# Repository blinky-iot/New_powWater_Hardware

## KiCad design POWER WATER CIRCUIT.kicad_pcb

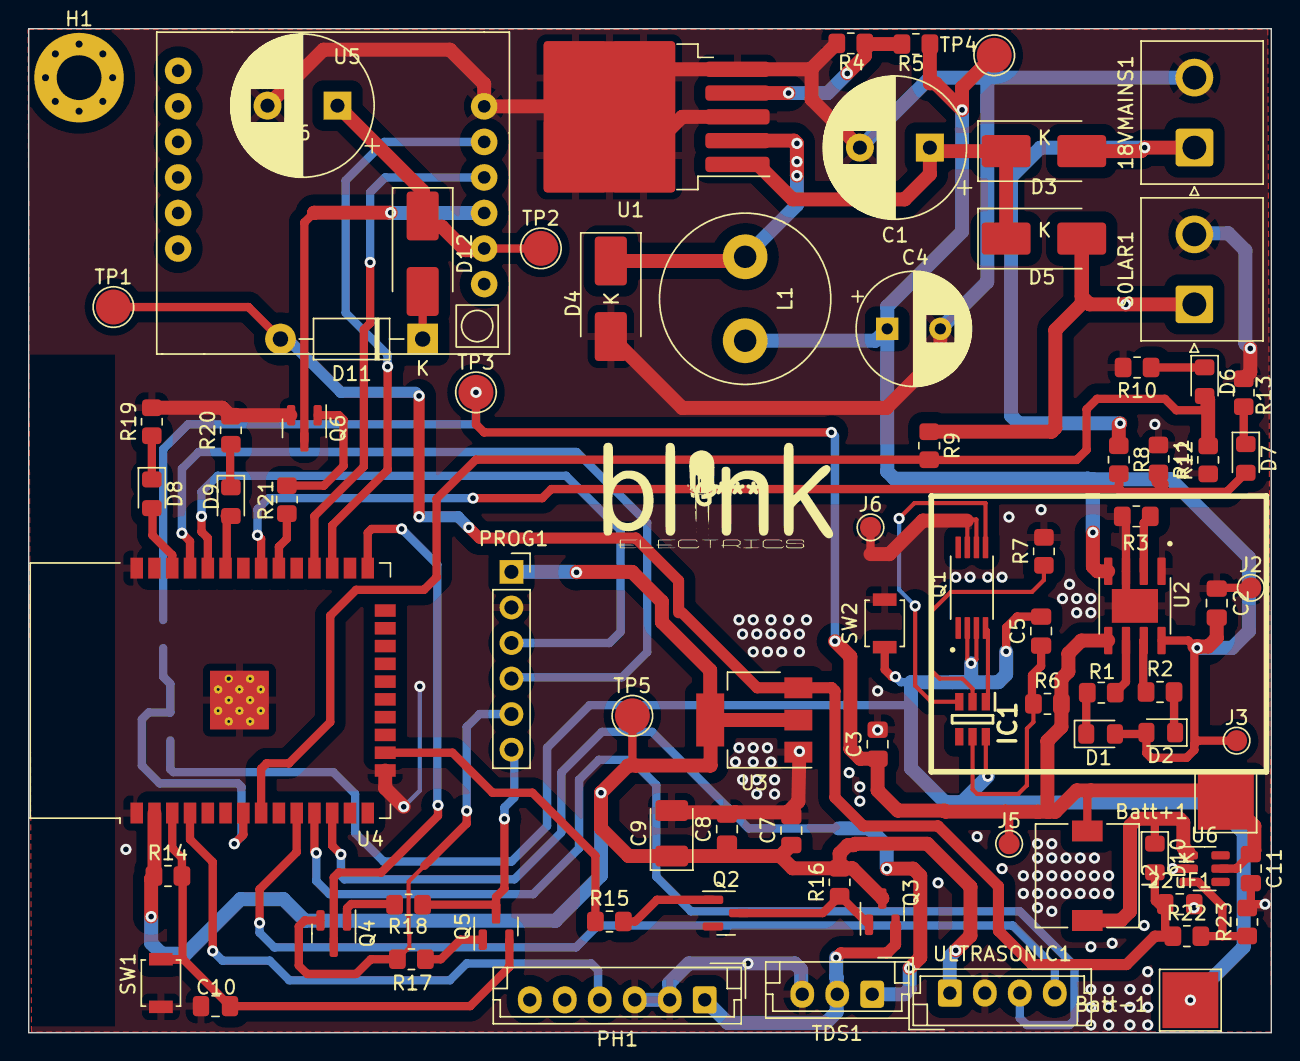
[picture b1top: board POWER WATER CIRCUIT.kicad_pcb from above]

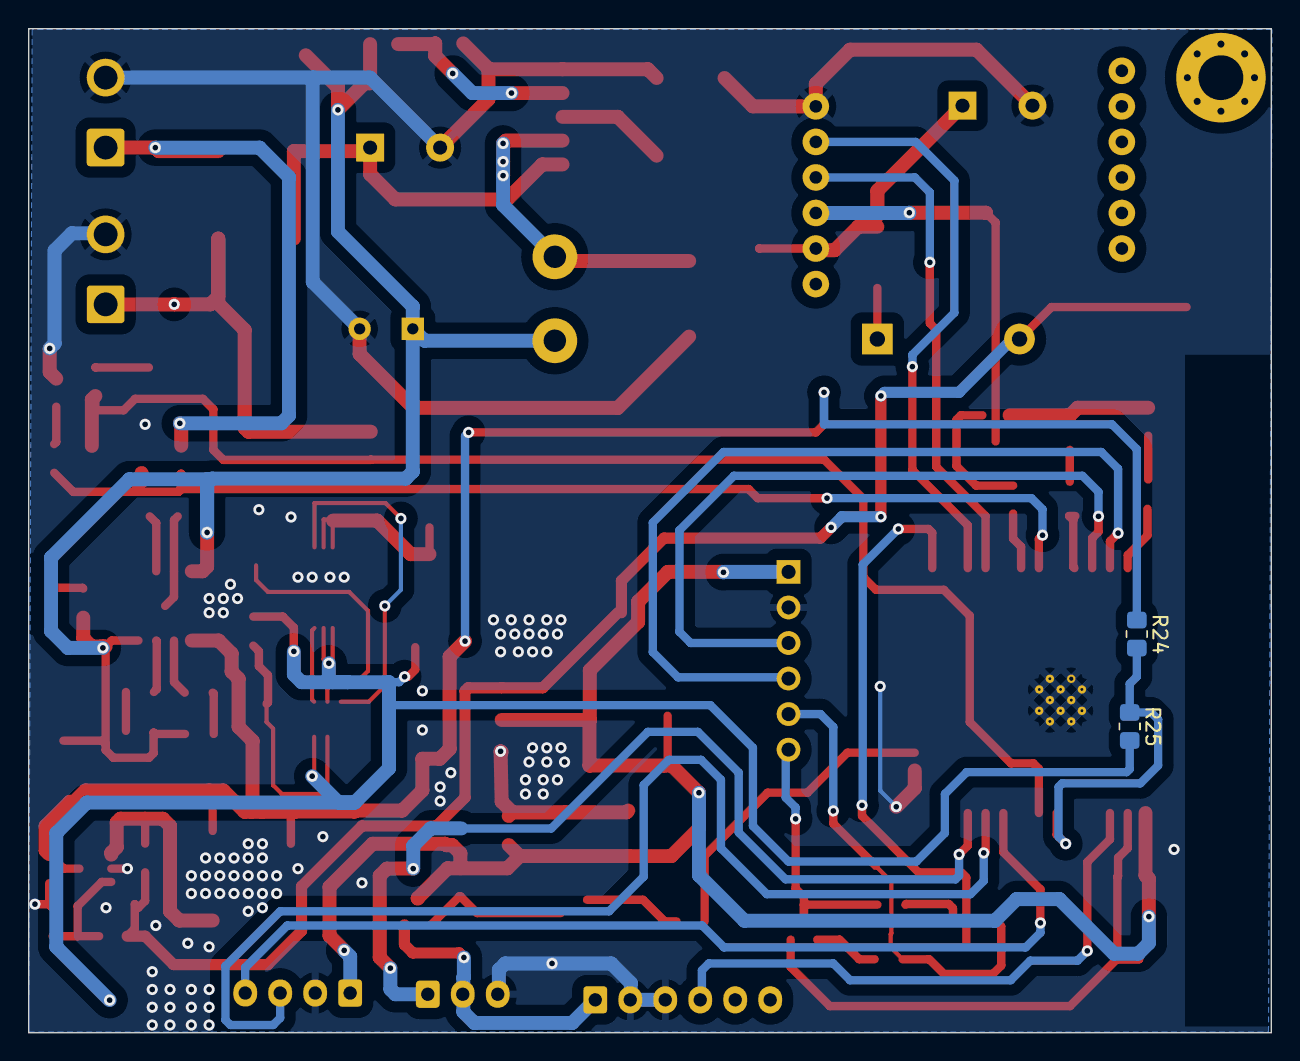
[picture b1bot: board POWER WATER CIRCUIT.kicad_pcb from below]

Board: 2 copper layers, 88.8 x 71.8 mm, 84 parts (2 on the bottom side), 54 nets.

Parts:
18VMAINS1: Screw_Terminal_01x02; JST_NV_B02P-NV_1x02_P5.00mm_Vertical
22uF1: C; C_0805_2012Metric_Pad1.18x1.45mm_HandSolder
Batt+1: BatteryPositive; TestPoint_Pad_4.0x4.0mm
Batt-1: BatteryNegative; TestPoint_Pad_4.0x4.0mm
C1, C6: 470uF; CP_Radial_D10.0mm_P5.00mm
C2, C3, C5, C7, C8, C10: 0.1uF; C_0805_2012Metric_Pad1.18x1.45mm_HandSolder
C4: 220uF; CP_Radial_D8.0mm_P3.80mm
C9: 220uF; CP_EIA-3528-15_AVX-H_Pad1.50x2.35mm_HandSolder
C11: 22UF; C_0805_2012Metric_Pad1.18x1.45mm_HandSolder
D1, D6, D8: GREEN_LED; LED_0805_2012Metric_Pad1.15x1.40mm_HandSolder
D2, D7, D9: RED_LED; LED_0805_2012Metric_Pad1.15x1.40mm_HandSolder
D3, D5, D12: 1N5820; D_SMB_Handsoldering
D4: 1N5819; D_SMB_Handsoldering
D10: 1N5820; D_0805_2012Metric_Pad1.15x1.40mm_HandSolder
D11: 1N4007; D_DO-41_SOD81_P10.16mm_Horizontal
H1: MountingHole_Pad; MountingHole_3.2mm_M3_Pad_Via
IC1: DW01; SOT95P280X135-6N
J2: IN-; TestPoint_Pad_D1.5mm
J3: IN+; TestPoint_Pad_D1.5mm
J5: OUT +; TestPoint_Pad_D1.5mm
J6: OUT -; TestPoint_Pad_D1.5mm
L1: 33uH; L_Radial_D12.0mm_P6.00mm_Murata_1900R
L2: 220uH; L_7.3x7.3_H3.5
PH1: Conn_01x06_Socket; JST_EH_B6B-EH-A_1x06_P2.50mm_Vertical
PROG1: Conn_01x06_Socket; PinSocket_1x06_P2.54mm_Vertical
Q1: FS8205A; SOP65P640X120-8N
Q2, Q4, Q5, Q6: BC817; SOT-23
Q3: IRLML5203; SOT-23
R1, R2, R4, R7: 1K; R_0805_2012Metric_Pad1.20x1.40mm_HandSolder
R3: 1.2K; R_0805_2012Metric_Pad1.20x1.40mm_HandSolder
R5: 3.9k; R_0805_2012Metric_Pad1.20x1.40mm_HandSolder
R6: 100; R_0805_2012Metric_Pad1.20x1.40mm_HandSolder
R8, R9: 10 K; R_0805_2012Metric_Pad1.20x1.40mm_HandSolder
R10, R13, R19, R20: 1k; R_0805_2012Metric_Pad1.20x1.40mm_HandSolder
R11, R12: 2.2 K; R_0805_2012Metric_Pad1.20x1.40mm_HandSolder
R14: 100K; R_0805_2012Metric_Pad1.20x1.40mm_HandSolder
R15: 10k; R_0805_2012Metric_Pad1.20x1.40mm_HandSolder
R16: 100k; R_0805_2012Metric_Pad1.20x1.40mm_HandSolder
R17, R18, R21: 10K; R_0805_2012Metric_Pad1.20x1.40mm_HandSolder
R22: 2.2k; R_0805_2012Metric_Pad1.20x1.40mm_HandSolder
R23: 300; R_0805_2012Metric_Pad1.20x1.40mm_HandSolder
R24: 120k; R_0805_2012Metric_Pad1.20x1.40mm_HandSolder
R25: 440k; R_0805_2012Metric_Pad1.20x1.40mm_HandSolder
S0LAR1: Screw_Terminal_01x02; JST_NV_B02P-NV_1x02_P5.00mm_Vertical
SW1, SW2: SW_MEC_5G; SW_SPST_B3U-1000P
TDS1: Conn_01x03_Socket; JST_EH_B3B-EH-A_1x03_P2.50mm_Vertical
TP1, TP2, TP3, TP4, TP5: TestPoint; TestPoint_Pad_D2.5mm
U1: LM2596S-ADJ; TO-263-5_TabPin3
U2: TP4056; SOP127P600X175-9N
U3: LM1117MP-3.3; SOT-223-3_TabPin2
U4: ESP32-WROOM-32
U5: SIM800L-CORE
U6: MT3608; SOT-23-6
ULTRASONIC1: Conn_01x04_Pin; JST_EH_B4B-EH-A_1x04_P2.50mm_Vertical

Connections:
4.0V: C6.1, D12.1 (K), TP2.1, U5.2 (VCC)
4.2: Batt+1.1, C3.1, C11.1, J5.1, L2.1, R6.2, R24.1, TP3.1, U2.5 (BAT), U6.5 (IN)
5V: 22uF1.1, D10.2 (A), D11.2 (A), R22.1, TP1.1, U3.3 (VI)
6V: C2.1, C4.1, D1.2 (A), D2.2 (A), J3.1, L1.2, R5.2, TP4.1, U2.4 (VCC), U2.8 (CE)
+3.3V: C7.1, C8.1, C9.1, PROG1.1, Q3.2 (S), R14.1, R16.2, TP5.1, U3.2 (VO), U4.2 (VDD), ULTRASONIC1.1
+ 18 V: C1.1, D3.1 (K), D5.1 (K), U1.1 (VIN)
BATERY VOLTAGE: R24.2, R25.1, U4.7 (IO35)
BT -VE: Batt-1.1, C5.2, IC1.6 (VSS), Q1.2 (S1_1), Q1.3 (S1_2), R25.2, SW2.1 (A)
CHRG: R2.1, U2.7 (~CHRG)
DC_Mains: 18VMAINS1.1, D3.2 (A), R8.1
DC_Solar: D5.2 (A), R9.1, S0LAR1.1
DTR: PROG1.5, Q4.2 (E), R17.1
GND: 18VMAINS1.2, 22uF1.2, C1.2, C2.2, C3.2, C4.2, C6.2, C7.2, C8.2, C9.2, C10.2, C11.2, D4.2 (A), J2.1, J6.1, PH1.2, PH1.3, PROG1.2, Q1.6 (S2_1), Q1.7 (S2_2), Q2.2 (E), Q6.2 (E), R3.1, R4.1, R7.2, R10.2, R11.1, R12.1, R13.2, R19.2, R20.2, R23.2, S0LAR1.2, SW1.2 (B), SW2.2 (B), TDS1.3, U1.3 (GND), U1.5 (~ON/OFF), U2.1 (TEMP), U2.3 (GND), U2.9 (EP), U3.1 (GND), U4.1 (GND), U4.15 (GND), U4.38 (GND), U4.39 (GND), U5.6 (GND), U6.2 (GND), ULTRASONIC1.2
GPIO0: Q4.3 (C), U4.25 (IO0)
GREEN_LED: D8.2 (A), U4.36 (IO22)
MCU_RX: PROG1.3, U4.34 (RXD0/IO3)
MCU_TX: PROG1.4, U4.35 (TXD0/IO1)
Mains_Available: D7.2 (A), R8.2, R11.2, U4.31 (IO19)
unnamed: D1.1 (K), R1.2
unnamed: D2.1 (K), R2.2
unnamed: D4.1 (K), L1.1, U1.2 (OUT)
unnamed: D6.1 (K), R10.1
unnamed: D7.1 (K), R13.1
unnamed: D8.1 (K), R19.1
unnamed: D9.1 (K), R20.1
unnamed: D10.1 (K), L2.2, U6.1 (SW)
unnamed: D11.1 (K), D12.2 (A)
unnamed: IC1.2 (CSI), R7.1
unnamed: IC1.3 (OC), Q1.5 (G2)
unnamed: IC1.1 (OD), Q1.4 (G1)
unnamed: C5.1, IC1.5 (VDD), R6.1
unnamed: Q2.1 (B), R15.2
unnamed: Q2.3 (C), Q3.1 (G), R16.1
unnamed: Q4.1 (B), R18.2
unnamed: Q5.1 (B), R17.2
unnamed: Q6.1 (B), R21.2
unnamed: R4.2, R5.1, U1.4 (FB)
unnamed: R3.2, U2.2 (PROG)
unnamed: R22.2, R23.1, U6.3 (FB)
PH_Analog: PH1.4, U4.4 (SENSOR_VP)
RED_LED: D9.2 (A), U4.33 (IO21)
RESET: C10.1, Q5.2 (E), R14.2, SW1.1 (A), U4.3 (EN)
RTS: PROG1.6, Q5.3 (C), R18.1
SIM_RST: Q6.3 (C), U5.3 (RST)
SIM_RST_PIN: R21.1, U4.30 (IO18)
SIM_RX: U4.28 (IO17), U5.4 (RXD)
SIM_TX: U4.27 (IO16), U5.5 (TXD)
STDBY: R1.1, U2.6 (~STDBY)
Sen_pwr: R15.1, U4.16 (IO13)
Solar_Voltage: D6.2 (A), R9.2, R12.2, U4.8 (IO32)
TurbidityAnalog: TDS1.1, U4.12 (IO27)
US_RX: U4.11 (IO26), ULTRASONIC1.3
US_TX: U4.10 (IO25), ULTRASONIC1.4
pwr: PH1.1, Q3.3 (D), TDS1.2

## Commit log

2024-10-18 added boost converter circuit
    changes
    1) Added battery voltage measurement circuit
    2) Push button to trigger the battery isolation mosfet
    3) Added voltage boost for the battery from 3.7 to 5v
2024-10-18 Final Changes before production
